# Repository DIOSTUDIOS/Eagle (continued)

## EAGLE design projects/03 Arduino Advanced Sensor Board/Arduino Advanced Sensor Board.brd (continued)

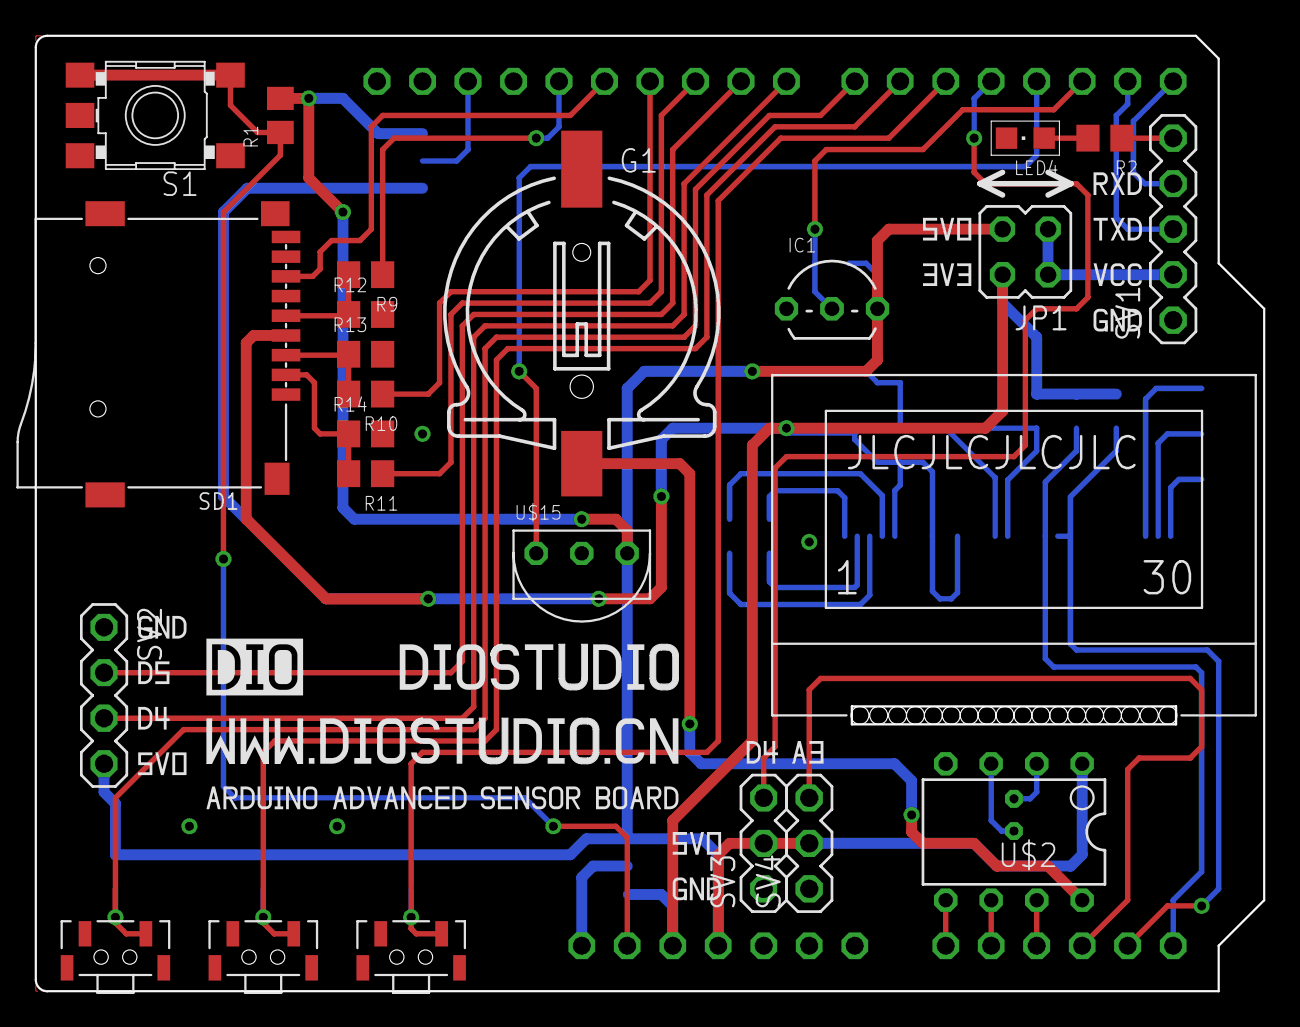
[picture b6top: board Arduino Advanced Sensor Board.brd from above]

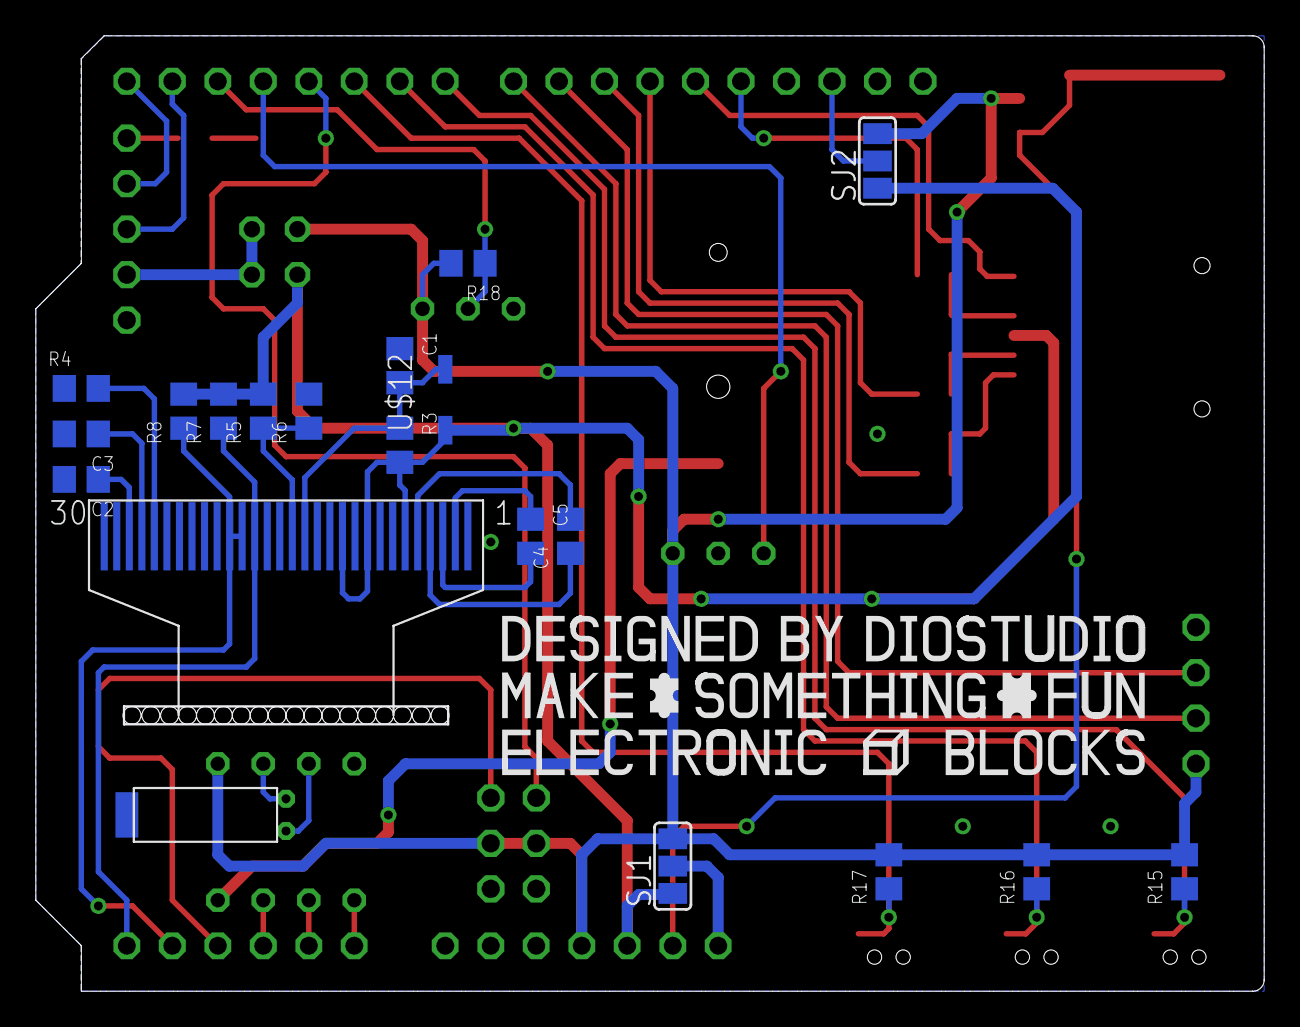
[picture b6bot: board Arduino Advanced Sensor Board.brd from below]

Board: 2 copper layers, 68.6 x 53.3 mm, 63 parts (20 on the bottom side), 44 nets.

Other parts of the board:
U$6, U$21, U$26: 5V0_050
U$7: 3V3_050
U$8, U$22, U$25: GND_050
U$9: RXD_050
U$10: TXD_050
U$11: VCC_050
U$16: ARDUINO_ADVANCED_SENSOR_BOARD
U$17: MAKE_SOMETHING_FUN_100
U$18: LOGO_100
U$19: DIOSTUDIO_100
U$20: WWW.DIOSTUDIO.CN_100
U$23, U$28: D4_050
U$24: A3_050
U$27: D5_050

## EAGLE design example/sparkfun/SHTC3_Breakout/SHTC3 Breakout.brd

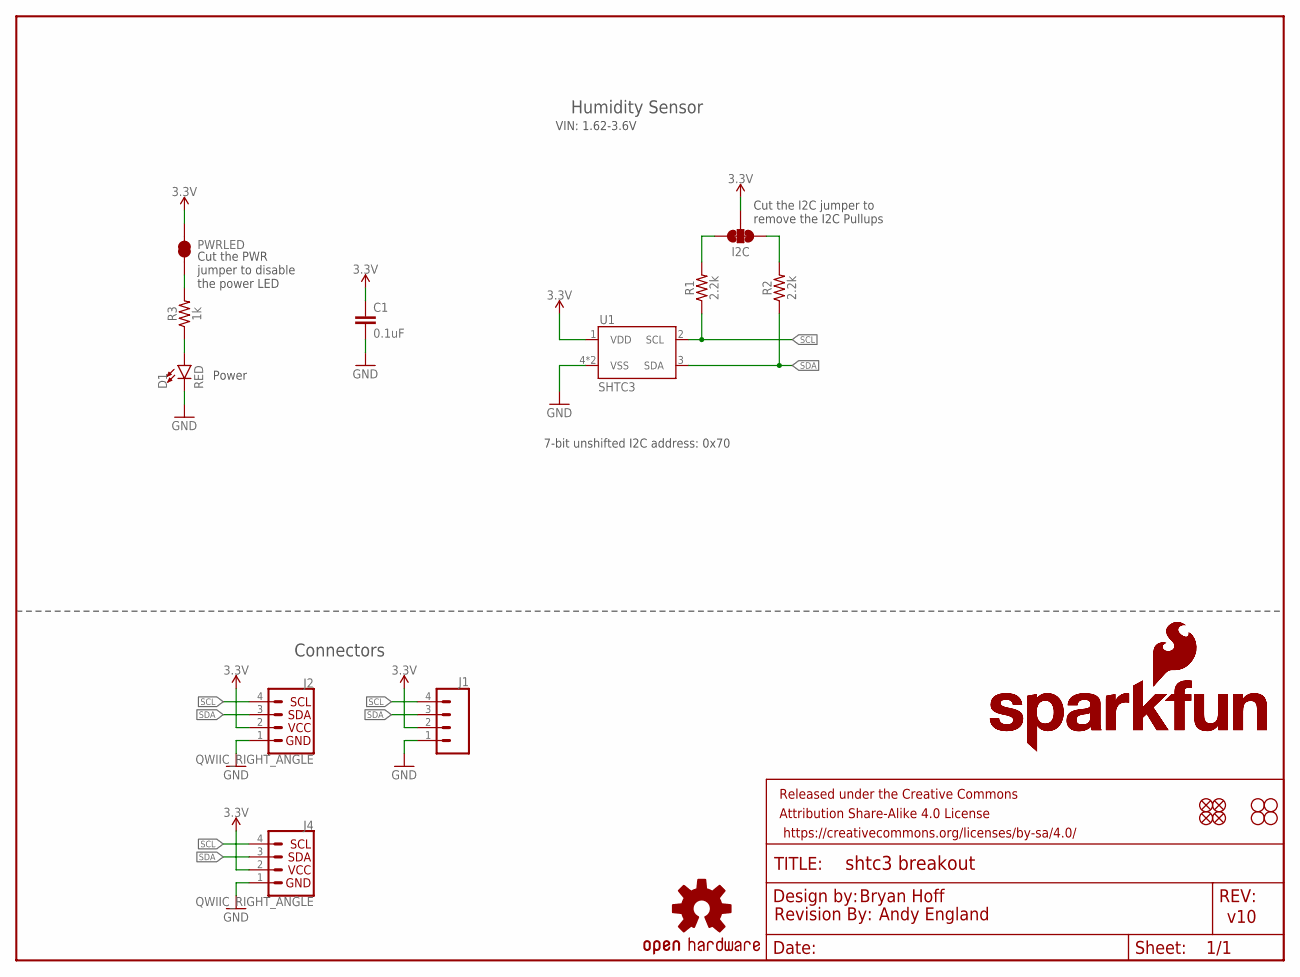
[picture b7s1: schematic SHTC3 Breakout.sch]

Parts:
C1: 0.1uF; 0603
D1: RED; LED-0603
FRAME1: FRAME-LETTER; CREATIVE_COMMONS
I2C: JUMPER-SMT_3_2-NC_TRACE_SILK; SMT-JUMPER_3_2-NC_TRACE_SILK
J1: CONN_041X04_NO_SILK; 1X04_NO_SILK
J2, J4: QWIIC_RIGHT_ANGLE; JST04_1MM_RA
JP1, JP2, JP5, JP6: FIDUCIALUFIDUCIAL; MICRO-FIDUCIAL
JP3, JP4, JP7, JP8: STAND-OFF
LOGO1: OSHW-LOGOMINI; OSHW-LOGO-MINI
LOGO2, LOGO3: SFE_LOGO_NAME_FLAME.1_INCH; SFE_LOGO_NAME_FLAME_.1
LOGO4: REVISION
PWRLED: JUMPER-SMT_2_NC_TRACE_SILK; SMT-JUMPER_2_NC_TRACE_SILK
R1, R2: 2.2k; 0603
R3: 1k; 0603
U1: SHTC3

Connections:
3.3V: C1.1, I2C.2, J1.2, J2.2, J4.2, PWRLED.2, U1.1 (VDD)
GND: C1.2, D1.C, J1.1, J2.1, J4.1, U1.4 (VSS), U1.5 (VSS)
unnamed: I2C.3, R1.2
unnamed: I2C.1, R2.2
unnamed: D1.A, R3.1
unnamed: PWRLED.1, R3.2
SCL: J1.4, J2.4, J4.4, R1.1, U1.2 (SCL)
SDA: J1.3, J2.3, J4.3, R2.1, U1.3 (SDA)

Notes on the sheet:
Bryan Hoff
v10
7-bit unshifted I2C address: 0x70
Power
Connectors
Cut the I2C jumper to remove the I2C Pullups
Humidity Sensor
Cut the PWR jumper to disable the power LED
Andy England
VIN: 1.62-3.6V

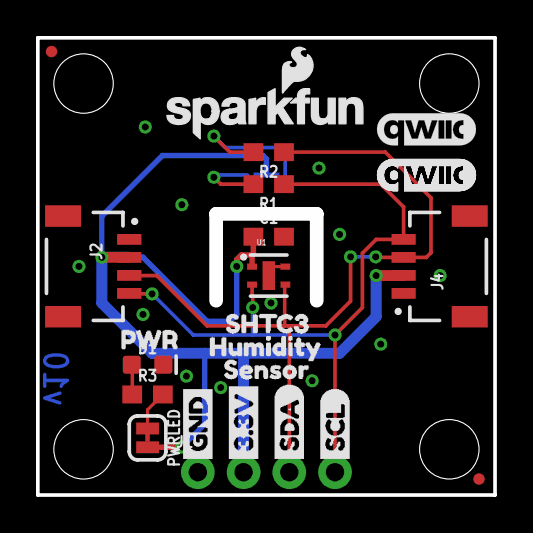
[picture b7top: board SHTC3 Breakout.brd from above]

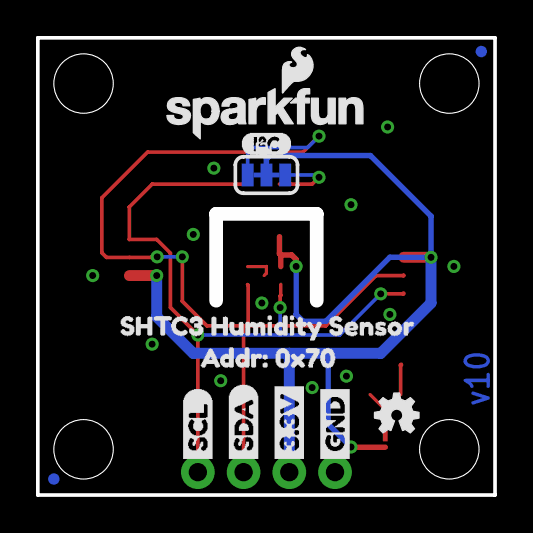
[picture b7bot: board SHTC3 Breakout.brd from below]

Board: 2 copper layers, 25.4 x 25.4 mm, 43 parts (12 on the bottom side), 8 nets.

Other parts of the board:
U$1: ADDR#_0X700
U$2: PWR_TO
U$3, U$22: GND1
U$4, U$21: 3#3V2
U$5, U$27: SDA8
U$6, U$26: SCL9
U$7: SHTC3_HUMIDITY_SENSOR2
U$8: _SHTC31
U$9: I_SUPER2_C-()-03
U$10: HUMIDITY2
U$11, U$13, U$14, U$15: QWIIC_5.5MM
U$12: SENSOR0

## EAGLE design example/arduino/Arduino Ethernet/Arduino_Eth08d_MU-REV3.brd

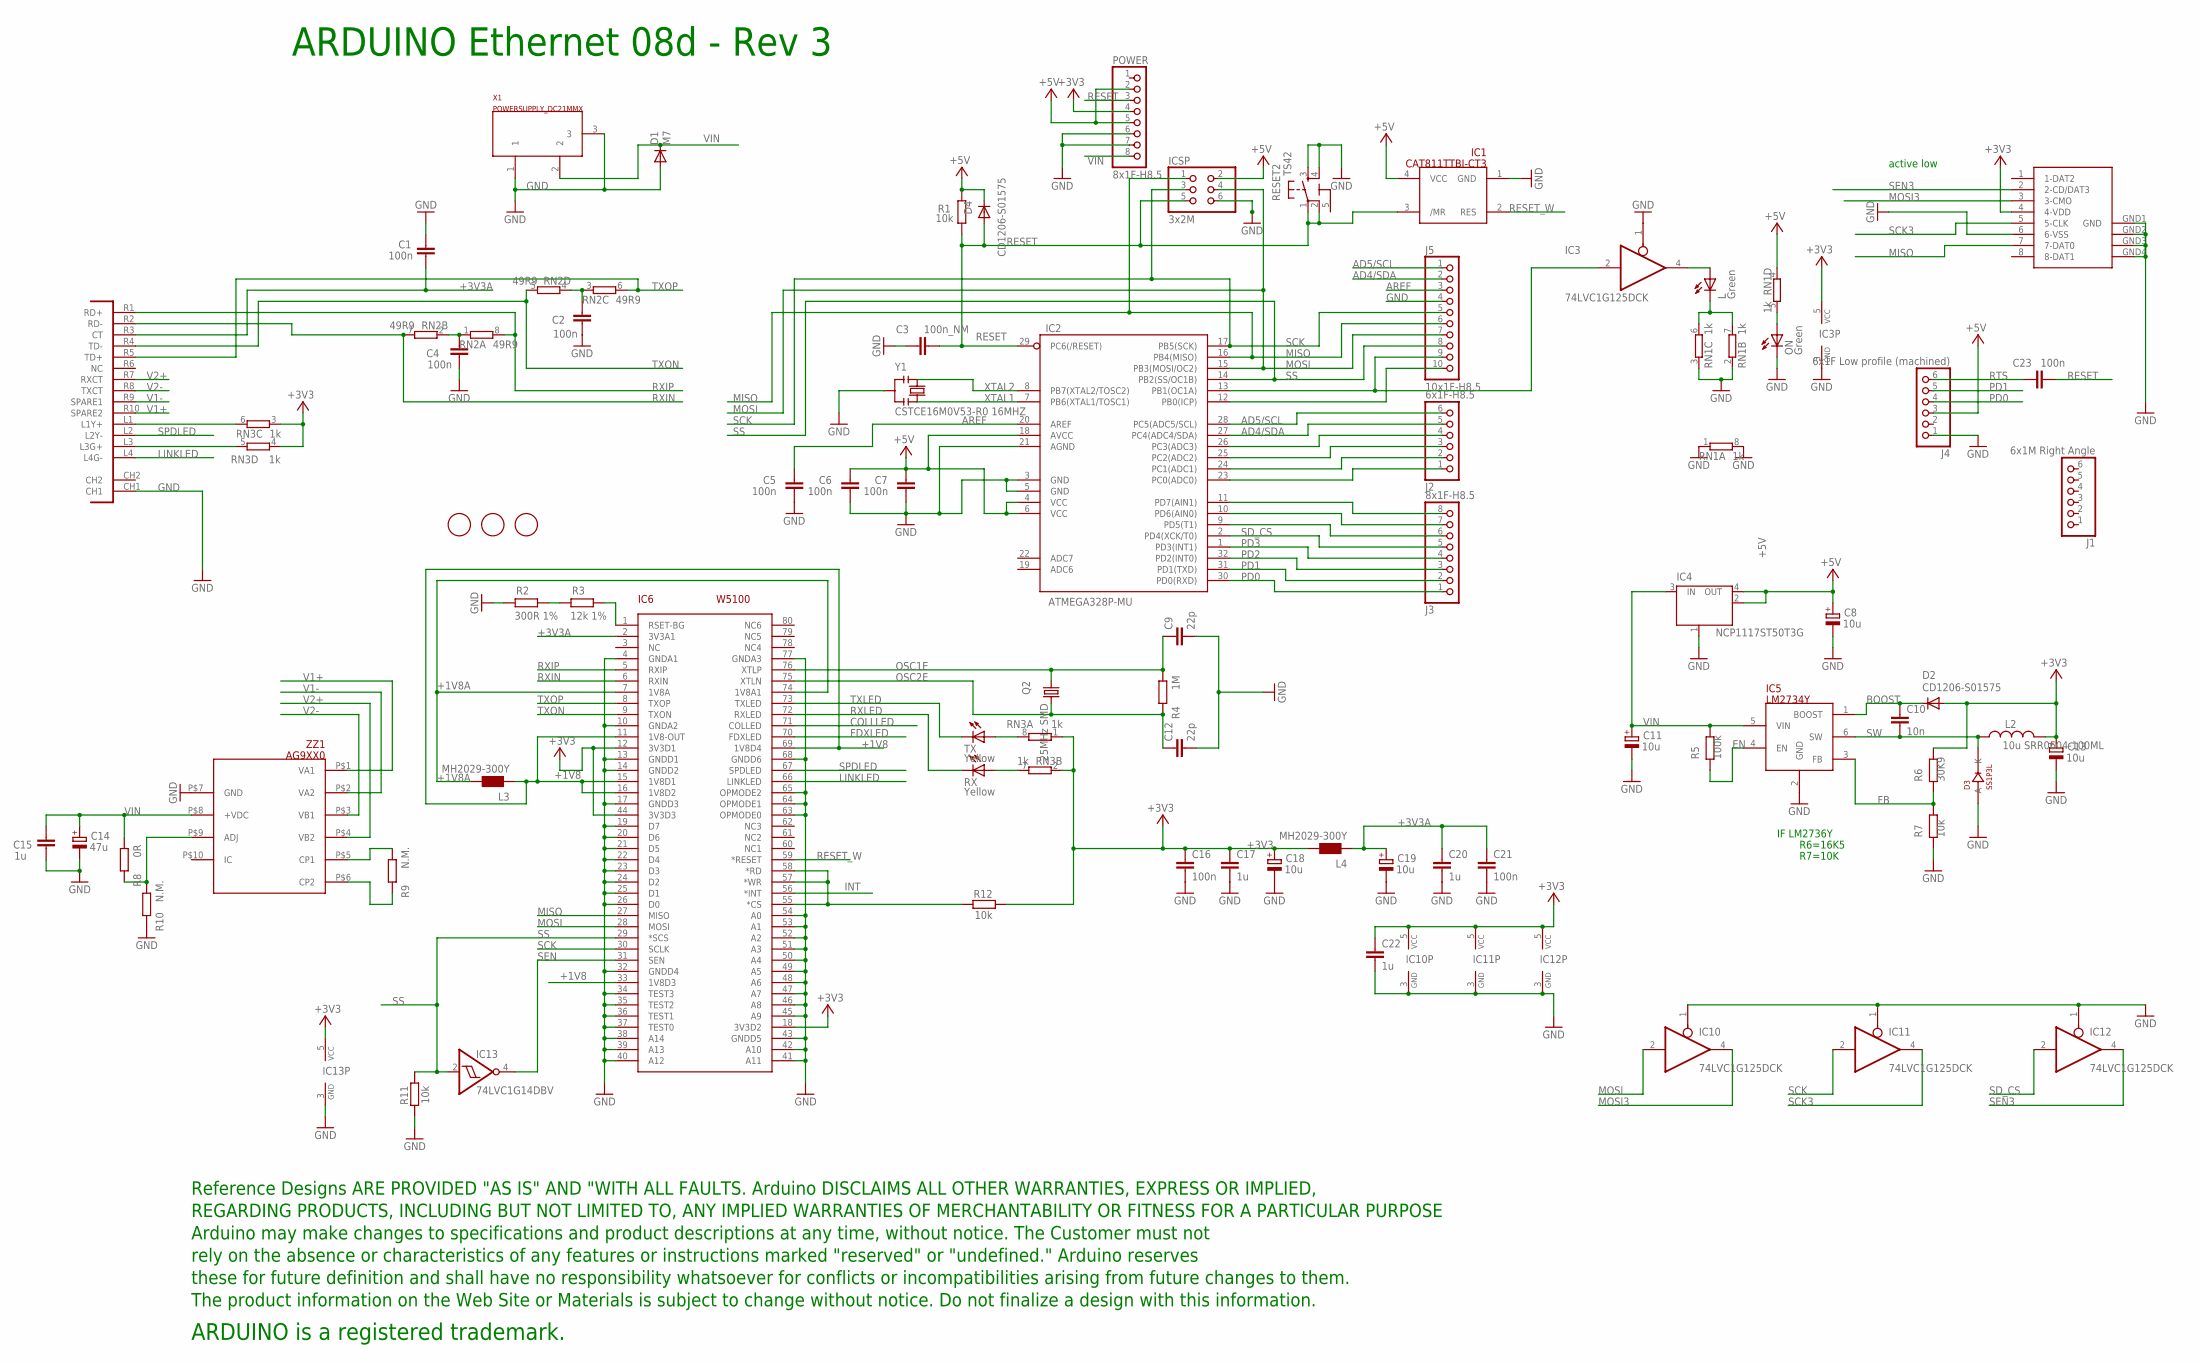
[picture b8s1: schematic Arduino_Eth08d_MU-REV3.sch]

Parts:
C1, C2, C4, C5, C6, C7, C16, C21, C23: 100n; C0603-ROUND
C3: 100n_NM; C0603-ROUND
C8, C11, C13, C18, C19: 10u; SMC_B
C9, C12: 22p; C0603-ROUND
C10: 10n; C0603-ROUND
C14: 47u; PANASONIC_D
C15, C17, C20, C22: 1u; C0603-ROUND
D1: M7; SMB
D2, D4: CD1206-S01575; MINIMELF
D3: SS1P3L; DO220AAL
FD1, FD2, FD3: FIDUCIALMOUNT; FIDUCIA-MOUNT
IC1: CAT811TTBI-CT3; SOT143
IC2: ATMEGA328P-MU; MLF32
IC3, IC10, IC11, IC12: 74LVC1G125DCK; SC70-5
IC4: NCP1117ST50T3G; LINEAR_SOT223
IC5: LM2734Y; SOT23-6
IC6: W5100; SQFP-S-10X10-80
IC13: 74LVC1G14DBV; SOT23-5
ICSP: 3x2M; 2X03
J1: 6x1M Right Angle; 1X06/90
J2: 6x1F-H8.5; 1X06
J3: 8x1F-H8.5; 1X08
J4: 6x1F Low profile (machined); 1X06-TH
J5: 10x1F-H8.5; 1X10
L: Green; CHIPLED_0805
L2: 10u SRR0604-100ML; SRR0604
L3, L4: MH2029-300Y; 0805
ON: Green; CHIPLED_0805
POWER: 8x1F-H8.5; 1X08
Q2: 25MHz SMD; HC49UP
R1, R7, R11, R12: 10k; R0603-ROUND
R2: 300R 1%; R0603-ROUND
R3: 12k 1%; R0603-ROUND
R4: 1M; R0603-ROUND
R5: 100k; R0603-ROUND
R6: 30K9; R0603-ROUND
R8: 0R; R0603-ROUND
R9, R10: N.M.; R0603-ROUND
RESET2: TS42
RN1, RN3: 1k; CAY16
RN2: 49R9; CAY16
RX: Yellow; CHIPLED_0805
TX: Yellow; CHIPLED_0805
U$1: POE-RJ45
U$2: DISCLAIMER
X1: POWERSUPPLY_DC21MMX; POWERSUPPLY_DC-21MM
X2: SDCARD-15TW-8821
Y1: CSTCE16M0V53-R0 16MHZ; RESONATOR
ZZ1: AG9XX0; AG9000

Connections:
5-GND: RESET2.5 (5-GND)
+1V8: IC6.11 (1V8-OUT), IC6.15 (1V8D1), IC6.16 (1V8D2), IC6.33 (1V8D3), IC6.69 (1V8D4), L3.1
+1V8A: IC6.7 (1V8A), IC6.74 (1V8A1), L3.2
+3V3: C13.+, C16.1, C17.1, C18.+, C22.1, D2.A, IC3.5 (VCC), IC6.12 (3V3D1), IC6.18 (3V3D2), IC6.44 (3V3D3), IC10.5 (VCC), IC11.5 (VCC), IC12.5 (VCC), IC13.5 (VCC), L2.P$2 (2), L4.2, POWER.4, R6.1, R12.2, RN3.1, RN3.2 (1), RN3.3 (1), RN3.4 (1), X2.4 (4-VDD)
+3V3A: C1.1, C19.+, C20.1, C21.1, IC6.2 (3V3A1), L4.1, U$1.R3 (CT)
+5V: C6.1, C7.1, C8.+, D4.C, IC1.4 (VCC), IC2.4 (VCC), IC2.6 (VCC), IC2.18 (AVCC), IC4.2 (OUT), IC4.4 (OUT), ICSP.2, J4.3, POWER.2, POWER.5, R1.2, RN1.4 (1)
AD4/SDA: IC2.27 (PC4(ADC4/SDA)), J2.5, J5.2
AD5/SCL: IC2.28 (PC5(ADC5/SCL)), J2.6, J5.1
AREF: C5.1, IC2.20 (AREF), J5.3
BOOST: C10.1, D2.C, IC5.1 (BOOST)
COLLLED: IC6.71 (COLLED)
EN: IC5.4 (EN), R5.2
FB: IC5.3 (FB), R6.2, R7.1
FDXLED: IC6.70 (FDXLED)
GND: C1.2, C2.1, C3.2, C4.1, C5.2, C6.2, C7.2, C8.-, C9.2, C11.-, C12.2, C13.-, C14.-, C15.1, C16.2, C17.2, C18.-, C19.-, C20.2, C21.2, C22.2, D1.A, D3.P$2 (A), IC1.1 (GND), IC2.3 (GND), IC2.5 (GND), IC2.21 (AGND), IC3.1 (OE), IC3.3 (GND), IC4.1 (GND/ADJ), IC5.2 (GND), IC6.4 (GNDA1), IC6.10 (GNDA2), IC6.13 (GNDD1), IC6.14 (GNDD2), IC6.17 (GNDD3), IC6.19 (D7), IC6.20 (D6), IC6.21 (D5), IC6.22 (D4), IC6.23 (D3), IC6.24 (D2), IC6.25 (D1), IC6.26 (D0), IC6.32 (GNDD4), IC6.34 (TEST3), IC6.35 (TEST2), IC6.36 (TEST1), IC6.37 (TEST0), IC6.38 (A14), IC6.39 (A13), IC6.40 (A12), IC6.41 (A11), IC6.42 (A10), IC6.43 (GNDD5), IC6.45 (A9), IC6.46 (A8), IC6.47 (A7), IC6.48 (A6), IC6.49 (A5), IC6.50 (A4), IC6.51 (A3), IC6.52 (A2), IC6.53 (A1), IC6.54 (A0), IC6.63 (OPMODE0), IC6.64 (OPMODE1), IC6.65 (OPMODE2), IC6.68 (GNDD6), IC6.77 (GNDA3), IC10.1 (OE), IC10.3 (GND), IC11.1 (OE), IC11.3 (GND), IC12.1 (OE), IC12.3 (GND), IC13.3 (GND), ICSP.6, J4.1, J5.4, ON.C, POWER.6, POWER.7, R2.2, R7.2, R10.2, R11.1, RESET2.3, RESET2.4, RN1.1, RN1.2 (1), RN1.3 (1), RN1.8 (2), U$1.CH1, X1.1, X1.3, X2.6 (6-VSS), X2.GND1 (GND), X2.GND2 (GND1), X2.GND3 (GND2), X2.GND4 (GND3), Y1.2, ZZ1.P$7 (GND)
INT: IC6.56 (*INT)
LINKLED: IC6.66 (LINKLED), U$1.L4 (L4G-)
MISO: IC2.16 (PB4(MISO)), IC6.27 (MISO), ICSP.1, J5.6, X2.7 (7-DAT0)
MOSI: IC2.15 (PB3(MOSI/OC2)), IC6.28 (MOSI), IC10.2 (I), ICSP.4, J5.7
MOSI3: IC10.4 (O), X2.3 (3-CMO)
unnamed: IC3.4 (O), L.A
unnamed: RN3.5 (2), U$1.L3 (L3G+)
unnamed: RN3.6 (2), U$1.L1 (L1Y+)
unnamed: IC2.13 (PB1(OC1A)), IC3.2 (I), J5.9
unnamed: L.C, RN1.6 (2), RN1.7 (2)
unnamed: ON.A, RN1.5 (2)
unnamed: RN3.8 (2), TX.A
unnamed: C2.2, RN2.3 (1), RN2.4 (1)
unnamed: IC2.9 (PD5(T1)), J3.6
unnamed: IC2.10 (PD6(AIN0)), J3.7
unnamed: IC2.11 (PD7(AIN1)), J3.8
unnamed: IC2.23 (PC0(ADC0)), J2.1
unnamed: IC2.24 (PC1(ADC1)), J2.2
unnamed: IC2.25 (PC2(ADC2)), J2.3
unnamed: IC2.26 (PC3(ADC3)), J2.4
unnamed: RN3.7 (2), RX.A
unnamed: C4.2, RN2.1, RN2.2 (1)
unnamed: R2.1, R3.2
unnamed: IC6.1 (RSET-BG), R3.1
unnamed: R9.1, ZZ1.P$5 (CP1)
unnamed: R9.2, ZZ1.P$6 (CP2)
unnamed: R8.2, R10.1, ZZ1.P$9 (ADJ)
unnamed: IC6.55 (*CS), IC6.57 (*WR), IC6.58 (*RD), R12.1
OSC1E: C9.1, IC6.76 (XTLP), Q2.1, R4.1
OSC2E: C12.1, IC6.75 (XTLN), Q2.2, R4.2
PD0: IC2.30 (PD0(RXD)), J3.1, J4.4
PD1: IC2.31 (PD1(TXD)), J3.2, J4.5
PD2: IC2.32 (PD2(INT0)), J3.3
PD3: IC2.1 (PD3(INT1)), J3.4
RESET: C3.1, C23.1, D4.A, IC1.3 (/MR), IC2.29 (PC6(/RESET)), ICSP.5, POWER.3, R1.1, RESET2.1, RESET2.2
RESET_W: IC1.2 (RES), IC6.59 (*RESET)
RTS: C23.2, J4.6
RXIN: IC6.6 (RXIN), RN2.7 (2), U$1.R2 (RD-)
RXIP: IC6.5 (RXIP), RN2.8 (2), U$1.R1 (RD+)
RXLED: IC6.72 (RXLED), RX.C
SCK: IC2.17 (PB5(SCK)), IC6.30 (SCLK), IC11.2 (I), ICSP.3, J5.5
SCK3: IC11.4 (O), X2.5 (5-CLK)
SD_CS: IC2.2 (PD4(XCK/T0)), IC12.2 (I), J3.5
SEN: IC6.31 (SEN), IC13.4 (O)
SEN3: IC12.4 (O), X2.2 (2-CD/DAT3)
SPDLED: IC6.67 (SPDLED), U$1.L2 (L2Y-)
SS: IC2.14 (PB2(SS/OC1B)), IC6.29 (*SCS), IC13.2 (I), J5.8, R11.2
SW: C10.2, D3.P$1 (K), IC5.6 (SW), L2.P$1 (1)
TXLED: IC6.73 (TXLED), TX.C
TXON: IC6.9 (TXON), RN2.5 (2), U$1.R4 (TD-)
TXOP: IC6.8 (TXOP), RN2.6 (2), U$1.R5 (TD+)
V1+: U$1.R10 (SPARE2), ZZ1.P$1 (VA1)
V1-: U$1.R9 (SPARE1), ZZ1.P$2 (VA2)
V2+: U$1.R7 (RXCT), ZZ1.P$4 (VB2)
V2-: U$1.R8 (TXCT), ZZ1.P$3 (VB1)
VIN: C11.+, C14.+, C15.2, D1.C, IC4.3 (IN), IC5.5 (VIN), POWER.8, R5.1, R8.1, X1.2, ZZ1.P$8 (+VDC)
WOL/IO: IC2.12 (PB0(ICP)), J5.10
XTAL1: IC2.7 (PB6(XTAL1/TOSC1)), Y1.3
XTAL2: IC2.8 (PB7(XTAL2/TOSC2)), Y1.1

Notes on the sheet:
ARDUINO Ethernet 08d - Rev 3
active low
IF LM2736Y
R6=16K5
R7=10K

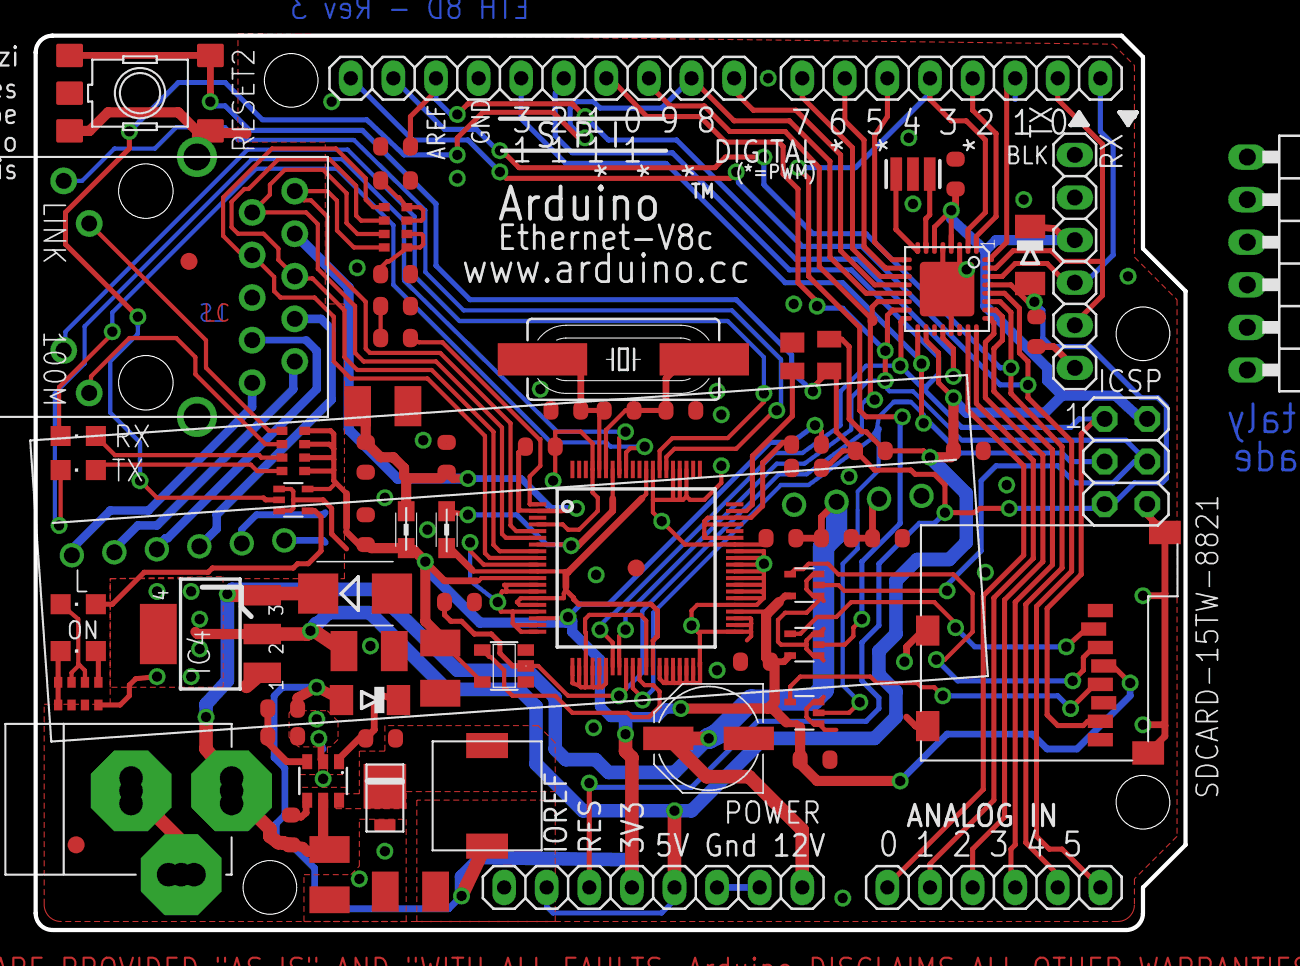
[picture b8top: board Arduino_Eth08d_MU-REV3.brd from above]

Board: 2 copper layers, 68.6 x 53.3 mm, 77 parts (1 on the bottom side), 70 nets.
